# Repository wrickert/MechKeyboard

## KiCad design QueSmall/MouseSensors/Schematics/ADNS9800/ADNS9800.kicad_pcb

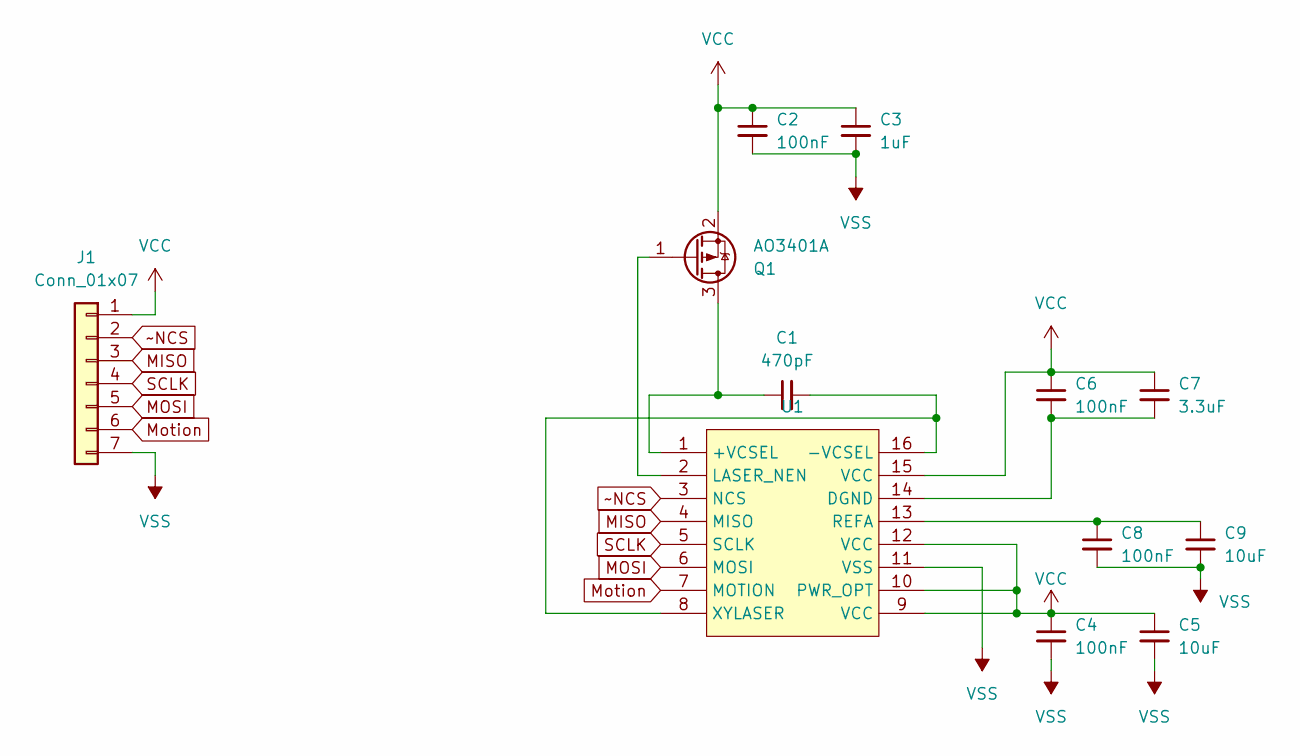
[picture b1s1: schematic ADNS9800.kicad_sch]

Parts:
C1: 470pF; C_0805_2012Metric
C2, C4, C6, C8: 100nF; C_0805_2012Metric
C3: 1uF; C_0805_2012Metric
C5, C9: 10uF; C_0805_2012Metric
C7: 3.3uF; C_0805_2012Metric
J1: Conn_01x07; PinHeader_1x07_P2.54mm_Vertical
Q1: AO3401A; SOT-23
U1: (no value)

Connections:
MISO: J1.3, U1.4 (MISO)
MOSI: J1.5, U1.6 (MOSI)
Motion: J1.6, U1.7 (MOTION)
unnamed: C1.1, Q1.3 (D), U1.1 (+VCSEL)
unnamed: Q1.1 (G), U1.2 (LASER_NEN)
unnamed: C1.2, U1.8 (XYLASER), U1.16 (-VCSEL)
unnamed: C6.2, C7.2, U1.14 (DGND)
unnamed: C8.1, C9.1, U1.13 (REFA)
SCLK: J1.4, U1.5 (SCLK)
VCC: C2.1, C3.1, C4.1, C5.1, C6.1, C7.1, J1.1, Q1.2 (S), U1.9 (VCC), U1.10 (PWR_OPT), U1.12 (VCC), U1.15 (VCC)
VSS: C2.2, C3.2, C4.2, C5.2, C8.2, C9.2, J1.7, U1.11 (VSS)
~NCS: J1.2, U1.3 (NCS)

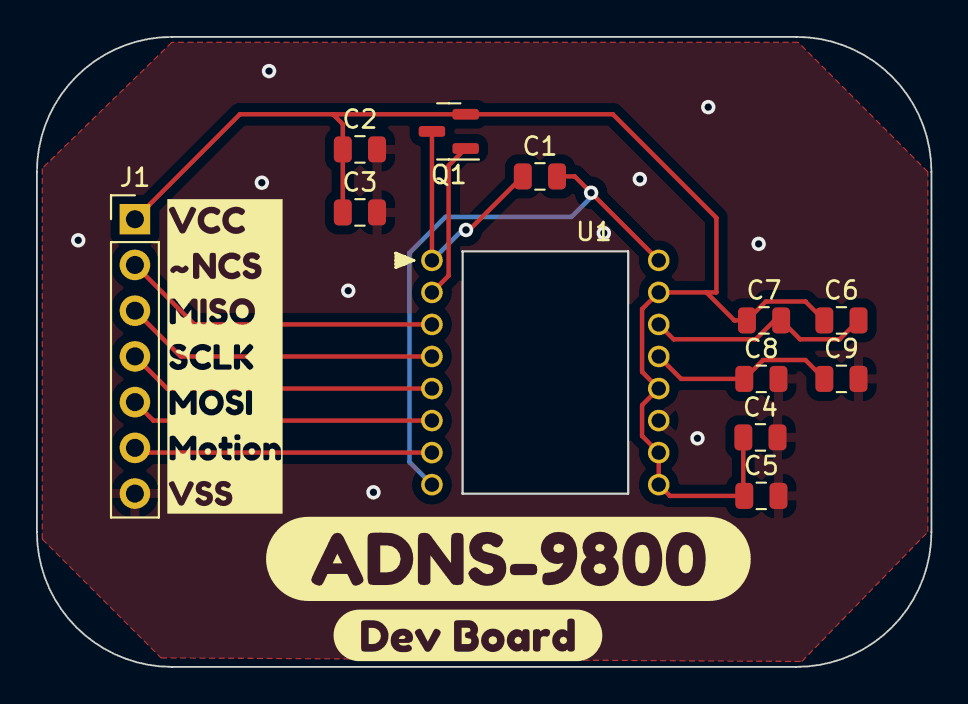
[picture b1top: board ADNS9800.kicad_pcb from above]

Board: 2 copper layers, 49.7 x 35.0 mm, 15 parts (0 on the bottom side), 12 nets.

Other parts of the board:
kibuzzard-65734003: G***; kibuzzard-65734003
kibuzzard-65734027: G***; kibuzzard-65734027
kibuzzard-65734037: G***; kibuzzard-65734037

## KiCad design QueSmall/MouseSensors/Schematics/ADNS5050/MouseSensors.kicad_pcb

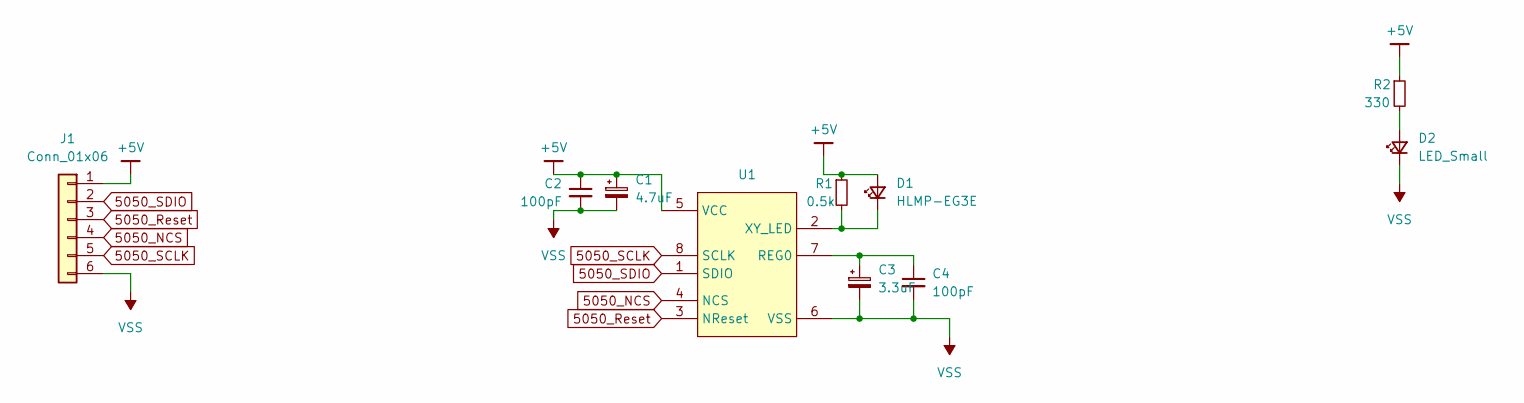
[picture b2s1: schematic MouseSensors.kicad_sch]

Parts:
C1: 4.7uF; C_0805_2012Metric
C2, C4: 100pF; C_0805_2012Metric
C3: 3.3uF; C_0805_2012Metric
D1: HLMP-EG3E; LED_D3.0mm
D2: LED_Small; LED_0805_2012Metric
J1: Conn_01x06; PinHeader_1x06_P2.54mm_Vertical
R1: 0.5k; R_0805_2012Metric
R2: 330; R_0805_2012Metric
U1: ADNS-5050

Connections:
5050_NCS: J1.4, U1.4 (NCS)
5050_Reset: J1.3, U1.3 (NReset)
5050_SCLK: J1.5, U1.8 (SCLK)
5050_SDIO: J1.2, U1.1 (SDIO)
+5V: C1.1, C2.1, D1.2 (A), J1.1, R1.1, R2.1, U1.5 (VCC)
unnamed: D1.1 (K), R1.2, U1.2 (XY_LED)
unnamed: D2.2 (A), R2.2
unnamed: C3.1, C4.1, U1.7 (REG0)
VSS: C1.2, C2.2, C3.2, C4.2, D2.1 (K), J1.6, U1.6 (VSS)

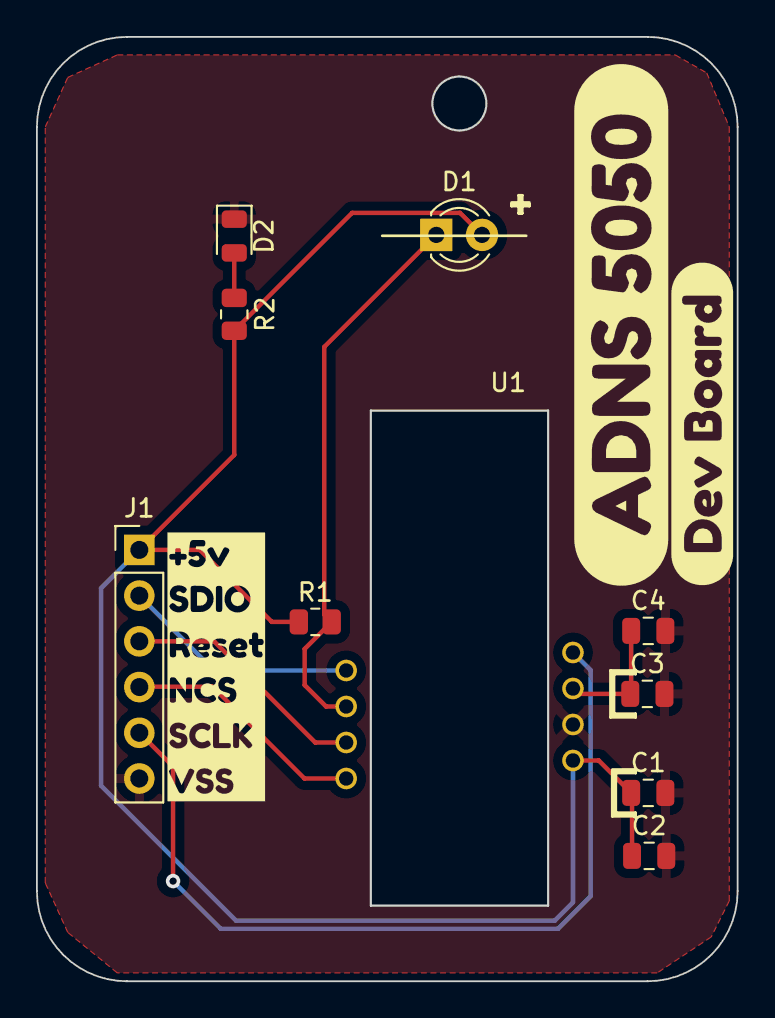
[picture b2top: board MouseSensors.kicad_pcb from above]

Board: 2 copper layers, 38.9 x 52.5 mm, 13 parts (0 on the bottom side), 9 nets.

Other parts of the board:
kibuzzard-65722F5A: G***; kibuzzard-65722F5A
kibuzzard-65722F43: G***; kibuzzard-65722F43
kibuzzard-65722FB8: G***; kibuzzard-65722FB8

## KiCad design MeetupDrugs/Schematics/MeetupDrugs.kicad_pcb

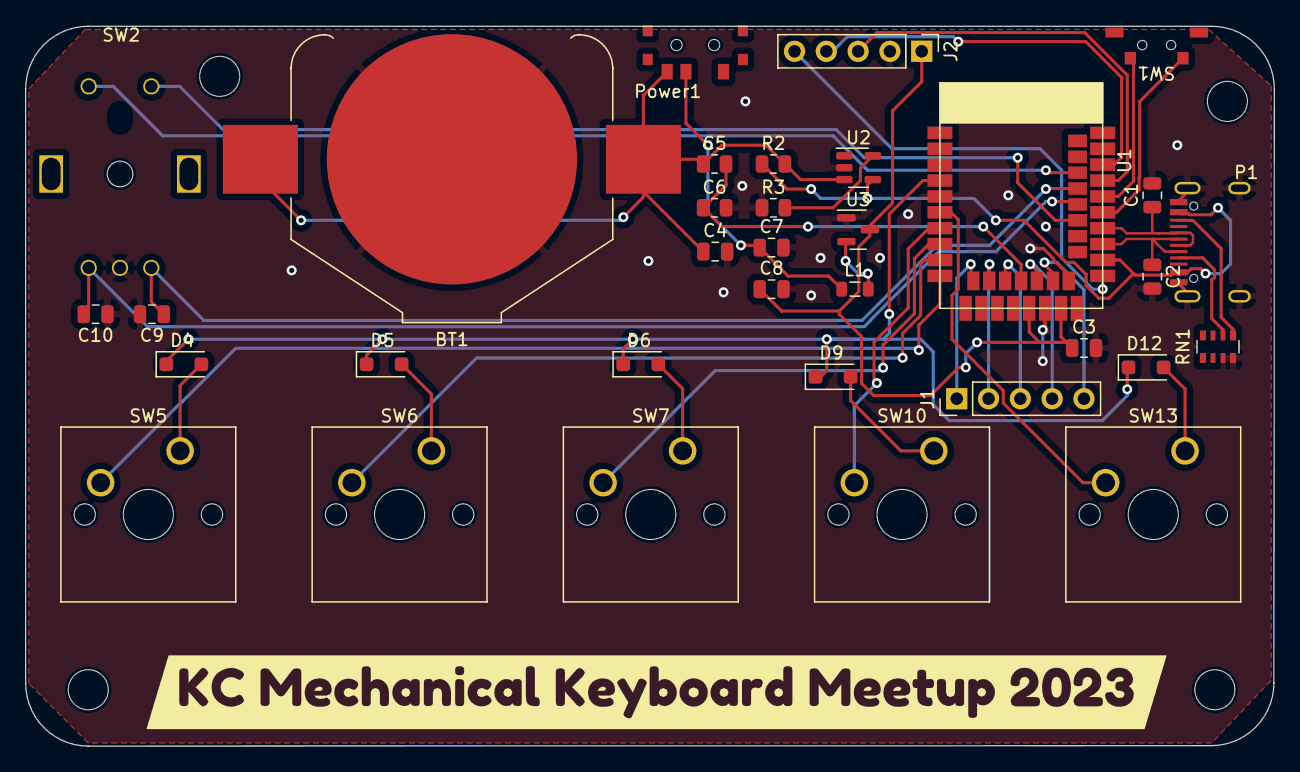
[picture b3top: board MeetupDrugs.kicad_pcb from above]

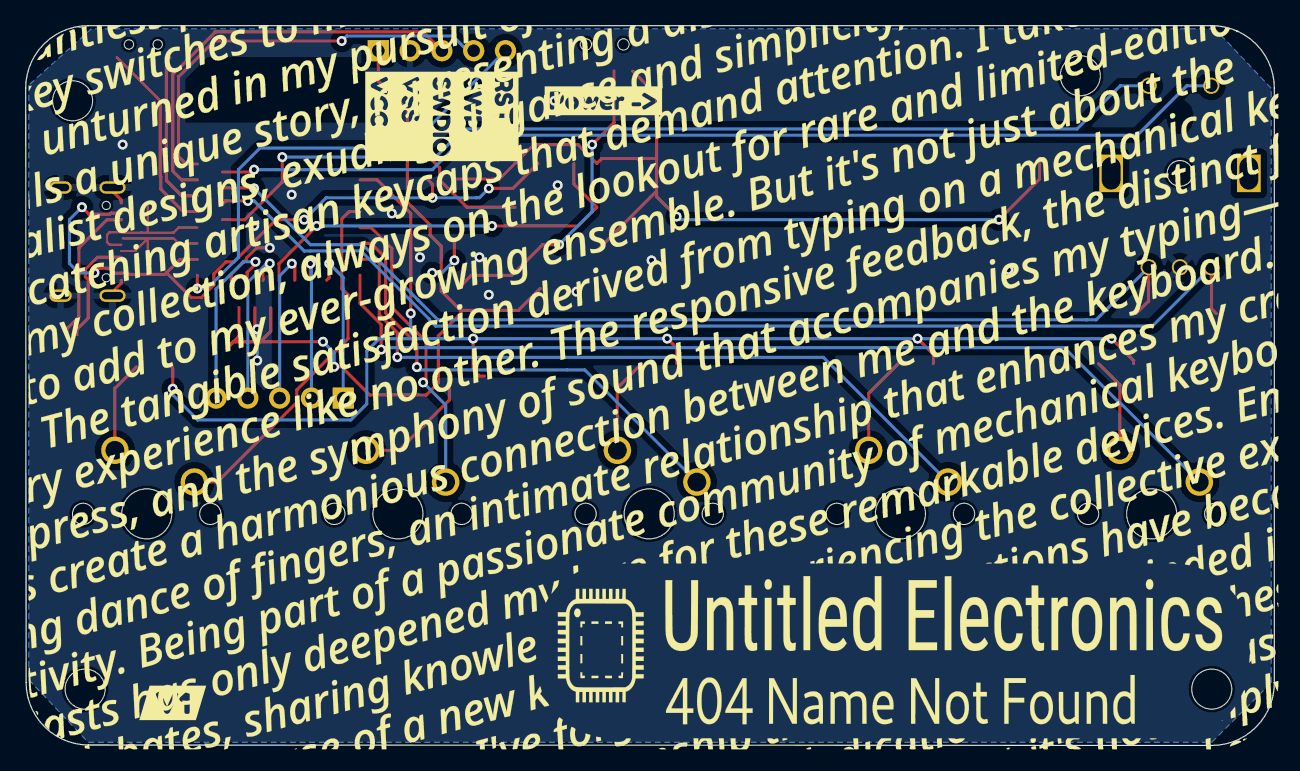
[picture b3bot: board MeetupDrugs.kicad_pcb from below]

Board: 2 copper layers, 99.8 x 57.5 mm, 39 parts (4 on the bottom side), 37 nets.

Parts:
BT1: Battery_Cell; BatteryHolder_Keystone_3008_1x2450
C1, C2: 20pF; C_0805_2012Metric
C3: 4.7uF; C_0805_2012Metric
C4, C7: 10uF; C_0805_2012Metric
C5: 800k; R_0805_2012Metric
C6: 2M; R_0805_2012Metric
C8: 22uF; C_0805_2012Metric
C9, C10: 100nF; C_0805_2012Metric
D4, D5, D6, D9, D12: D; D_SOD-123F
J1, J2: Conn_01x05; PinHeader_1x05_P2.54mm_Vertical
L1: 10uH; L_0805_2012Metric
P1: USB_C_Plug_corrected; USB_C_Receptical-Jing
Power1: SW3; SK-3296S_switch
R2: Charger Bypass; R_0805_2012Metric
R3: R_Small; R_0805_2012Metric
RN1: 5.1k; R_Array_Convex_4x0603
Ref**: Val**; MeetupBack
SW1: SW_SPST; TS36CA-0.7
SW2: Rotary_Encoder_Switch; EC11L1524E03_Rotary_Encoder
SW5, SW6, SW7, SW10, SW13: Switch; SW_Cherry_MX_1.00u_PCB
U1: E73-2G4M08S1C
U2: HX4055M; SOT-23-5
U3: SOT-23
kibuzzard-648A54B3: G***; kibuzzard-648A54B3
kibuzzard-648A54D0: G***; kibuzzard-648A54D0
kibuzzard-648A556D: G***; kibuzzard-648A556D
kibuzzard-648A5551: G***; kibuzzard-648A5551

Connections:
/C1: SW5.2, U1.10 (P0.30/A6)
/C2: SW6.2, U1.9 (P0.31/A7)
/C3: SW7.2, U1.8 (P0.29/A5)
/C4: SW10.2, U1.7 (P0.02/A0)
/C5: SW13.2, U1.6 (P1.13)
/R1: D4.1 (K), D5.1 (K), D6.1 (K), D9.1 (K), D12.1 (K), U1.4 (P0.28/A4)
/RotaryA: C9.1, SW2.B, U1.36 (P1.0)
/RotaryB: C10.2, SW2.A, U1.34 (P0.22)
/RotaryS1: SW2.S1, U1.38 (P1.02)
/RotaryS2: SW2.S2, U1.32 (P0.20)
D+: C1.1, P1.A6 (D+), P1.B6 (D+), U1.31 (D+)
D-: C2.1, P1.A7 (D-), P1.B7 (D-), U1.29 (D-)
unnamed: D4.2 (A), SW5.1
unnamed: D5.2 (A), SW6.1
unnamed: D6.2 (A), SW7.1
unnamed: D9.2 (A), SW10.1
unnamed: D12.2 (A), SW13.1
unnamed: J1.1, U1.12 (P0.26)
unnamed: J1.2, U1.14 (P0.06)
unnamed: J1.3, U1.16 (P0.08)
unnamed: J1.4, U1.20 (P0.12)
unnamed: J1.5, U1.22 (P0.07)
unnamed: P1.A5 (CC), RN1.6 (R3.2)
unnamed: P1.B5 (VCONN), RN1.5 (R4.2)
unnamed: C7.1, L1.1, Power1.2 (B)
unnamed: SW1.1 (A), U1.33 (P0.13)
unnamed: SW1.2 (B), U1.35 (P0.24)
unnamed: R3.2, U2.5 (PROG)
unnamed: L1.2, U3.2 (LX)
RST: J2.5, U1.26 (RST)
SWD: J2.4, U1.39 (SWD)
SWDIO: J2.3, U1.37 (SWDIO)
VBUS: P1.A4 (VBUS), P1.A9 (VBUS), P1.B4 (VBUS), P1.B9 (VBUS), R2.1, U1.27 (VBUS), U2.4 (VCC)
VBat: C5.2, C6.1, U1.18 (P0.04/A2)
VCC: C3.1, C8.1, J2.1, U1.19 (VDD), U1.23 (VDDH), U3.3 (VOUT)
VDDA: BT1.1 (+), C4.1, C5.1, Power1.1 (A), R2.2, U2.3 (Bat)
VSS: BT1.2 (-), C1.2, C2.2, C3.2, C4.2, C6.2, C7.2, C8.2, C9.2, C10.1, J2.2, P1.A1 (GND), P1.A12 (GND), P1.B1 (GND), P1.B12 (GND), P1.S1 (SHIELD), R3.1, RN1.3 (R3.1), RN1.4 (R4.1), SW2.C, U1.5 (GND), U1.21 (GND), U1.24 (GND), U2.2 (Gnd), U3.1 (VSS)

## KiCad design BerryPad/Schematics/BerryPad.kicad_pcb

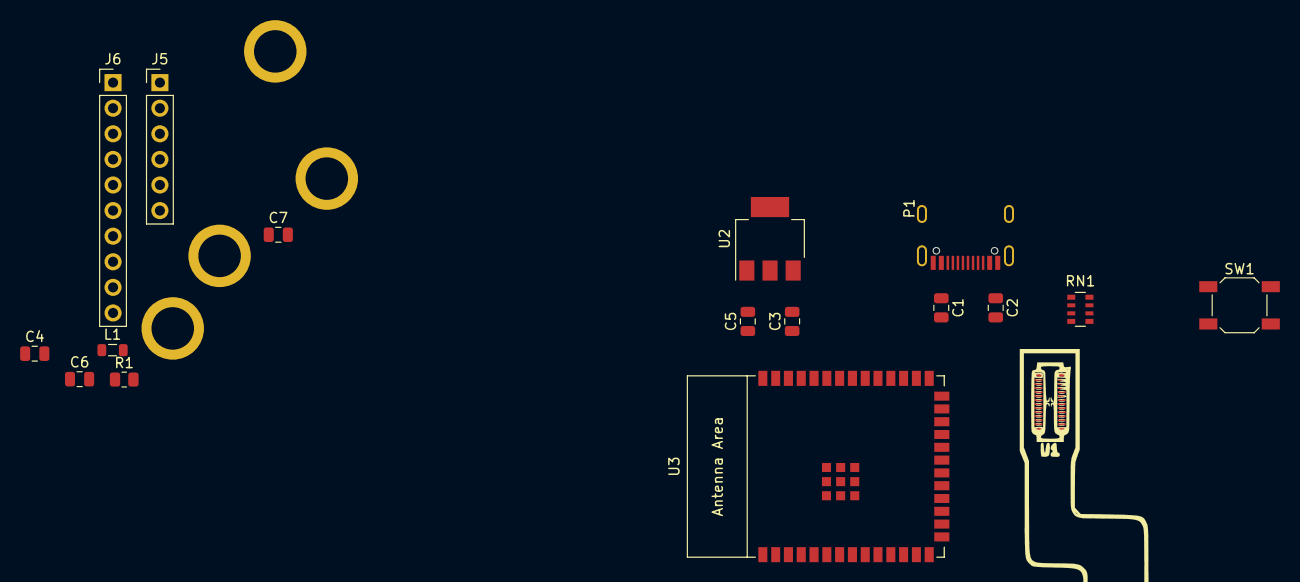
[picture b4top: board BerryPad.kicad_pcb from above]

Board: 2 copper layers, 22 parts (1 on the bottom side), 36 nets, no tracks yet.

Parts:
C1, C2: 20pF; C_0805_2012Metric
C3, C5: 1uF; C_0805_2012Metric
C4: 22uF; C_0805_2012Metric
C6, C7: 100nF; C_0805_2012Metric
J1, J2, J3, J4: Conn_01x01; SMD Spacer M2.5
J5: Program; PinHeader_1x06_P2.54mm_Vertical
J6: Conn_01x10; PinHeader_1x10_P2.54mm_Vertical
L1: L_Small; L_0805_2012Metric
P1: USB_C_Plug_corrected; USB_C_Receptical-Jing
R1: 1k; R_0805_2012Metric
RN1: 5.1k; R_Array_Convex_4x0603
Ref**: Val**; BerryPadKbd
SW1: Boot Mode; SW_SPST_SKQG_WithoutStem
U1: BBQ10KBD; BM14B(0.8)-24DS-0.4V(53)
U2: TLV1117-33; SOT-223-3_TabPin2
U3: ESP32-S2-SOLO

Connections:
1: J6.1, U3.39 (GPIO1/TOUCH1/ADC1_CH0)
2: J6.2, U3.38 (GPIO2/TOUCH2/ADC1_CH1)
3: J6.3, U3.15 (GPIO3/TOUCH3/ADC1_CH2)
4: J6.4, U3.35 (MTMS/GPIO42)
5: J6.5, U3.26 (GPIO45)
6: J6.6, U3.16 (GPIO46)
7: J6.7, U3.24 (SPIIO4/GPIO33/FSPIHD)
8: J6.8, U3.25 (SPIIO5/GPIO34/FSPICS0)
9: J6.9, U3.28 (SPIIO6/GPIO35/FSPID)
10: J6.10, U3.29 (SPIIO7/GPIO36/FSPICLK)
/D+: C1.1, P1.A6 (D+), P1.B6 (D+), U3.14 (GPIO20/U1CTS/ADC2_CH9/CLK_OUT1/USB_D+)
/D-: C2.1, P1.A7 (D-), P1.B7 (D-), U3.13 (GPIO19/U1RTS/ADC2_CH8/CLK_OUT2/USB_D-)
COL1: U1.7 (COL1), U3.4 (GPIO4/TOUCH4/ADC1_CH3)
COL2: U1.9 (COL2), U3.5 (GPIO5/TOUCH5/ADC1_CH4)
COL3: U1.10 (COL3), U3.6 (GPIO6/TOUCH6/ADC1_CH5)
COL4: U1.17 (COL4), U3.7 (GPIO7/TOUCH7/ADC1_CH6)
COL5: U1.19 (COL5), U3.12 (GPIO8/TOUCH8/ADC1_CH7)
LEDA1: U1.26 (LEDA_1_2), U3.9 (GPIO16/U0CTS/ADC2_CH5/XTAL_32K_N)
LEDA2: U1.24 (LEDA_3_4), U3.10 (GPIO17/U1TXD/ADC2_CH6/DAC_1)
unnamed: P1.A5 (CC), RN1.7 (R2.2)
unnamed: P1.B5 (VCONN), RN1.8 (R1.2)
unnamed: L1.1, U1.4 (AGND)
ROW1: U1.6 (ROW1), U3.17 (GPIO9/TOUCH9/ADC1_CH8/FSPIHD)
ROW2: U1.8 (ROW2), U3.18 (GPIO10/TOUCH10/ADC1_CH9/FSPICS0/FSPIIO4)
ROW3: U1.18 (ROW3), U3.19 (GPIO11/TOUCH11/ADC2_CH0/FSPID/FSPIIO5)
ROW4: U1.20 (ROW4), U3.20 (GPIO12/TOUCH12/ADC2_CH1/FSPICLK/FSPIIO6)
ROW5: U1.21 (ROW5), U3.21 (GPIO13/TOUCH13/ADC2_CH2/FSPIQ/FSPIIO7)
ROW6: U1.22 (ROW6), U3.22 (GPIO14/TOUCH14/ADC2_CH3/FSPIWP/FSPIDQS)
ROW7: U1.27 (ROW7), U3.8 (GPIO15/U0RTS/ADC2_CH4/XTAL_32K_P)
RX: J5.5, U3.36 (U0RXD/GPIO44/CLK_OUT2)
Reset: C7.1, J5.6, R1.1, U3.3 (EN)
TX: J5.4, U3.37 (U0TXD/GPIO43/CLK_OUT1)
TopLeft: J5.3, SW1.2, U3.27 (GPIO0)
VBUS: C3.2, P1.A4 (VBUS), P1.A9 (VBUS), P1.B4 (VBUS), P1.B9 (VBUS), U2.3 (VI)
VCC: C4.1, C5.2, C6.1, J5.1, R1.2, U1.2 (MIC_VDD), U2.2 (VO), U3.2 (3V3)
VSS: C1.2, C2.2, C3.1, C4.2, C5.1, C6.2, C7.2, J5.2, L1.2, P1.A1 (GND), P1.A12 (GND), P1.B1 (GND), P1.B12 (GND), P1.S1 (SHIELD), RN1.1 (R1.1), RN1.2 (R2.1), SW1.1, U1.1 (GND), U1.5 (GND), U1.11 (GND), U1.12 (GND), U1.13 (GND), U1.14 (GND), U1.15 (GND), U1.16 (GND), U1.23 (LEDK_2_3), U1.25 (LEDK_1_4), U1.28 (GND), U2.1 (GND), U3.1 (GND), U3.40 (GND), U3.41 (GND)

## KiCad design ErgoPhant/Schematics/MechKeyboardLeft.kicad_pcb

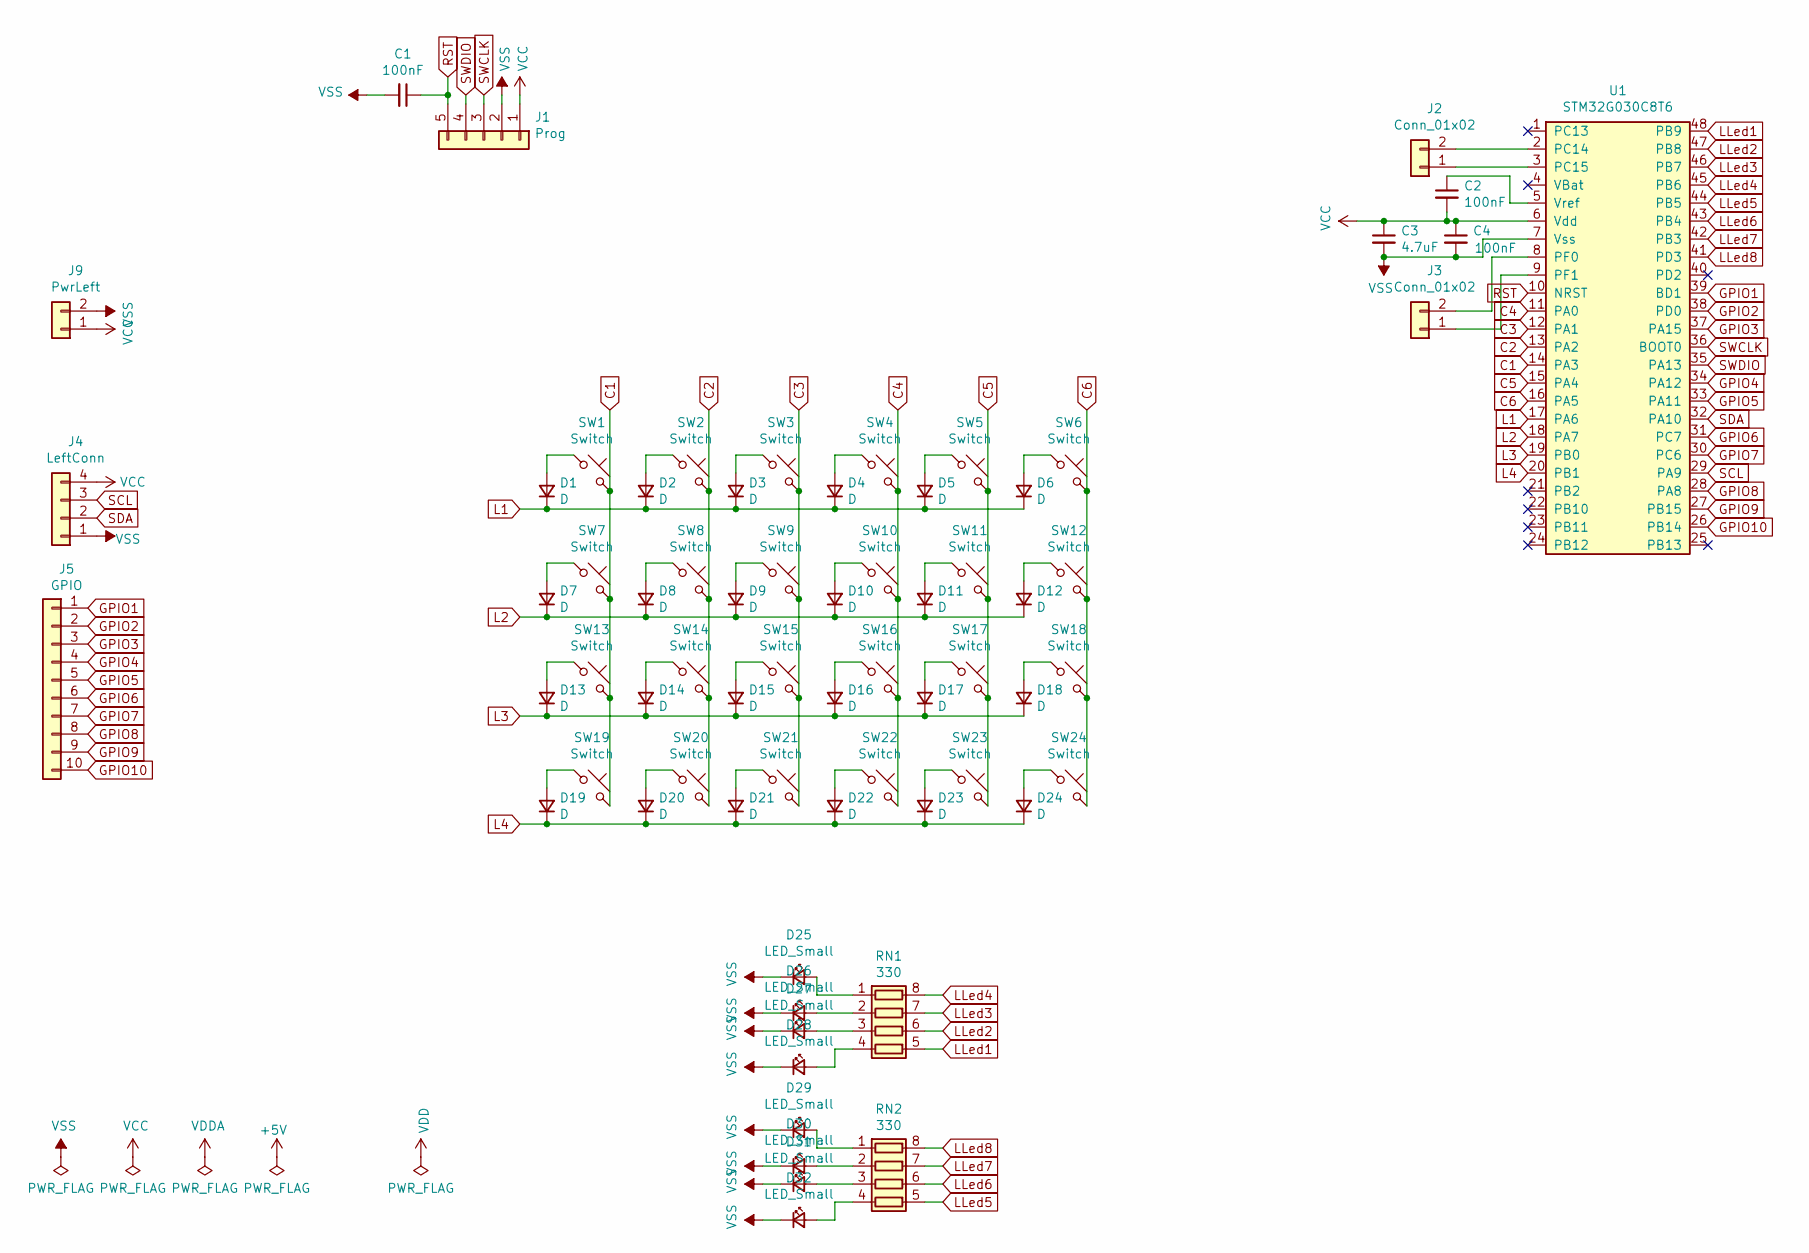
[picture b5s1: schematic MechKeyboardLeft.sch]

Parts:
C1, C2, C4: 100nF; C_0805_2012Metric
C3: 4.7uF; C_0805_2012Metric
D1, D2, D3, D4, D5, D6, D7, D8, D9, D10, D11, D12, D13, D14, D15, D16, D17, D18, D19, D20, D21, D22, D23, D24: D; D_0805_2012Metric
D25, D26, D27, D28, D29, D30, D31, D32: LED_Small; LED_0805_2012Metric
J1: Prog; PinHeader_1x05_P2.54mm_Vertical
J2: Conn_01x02; PinHeader_1x02_P2.54mm_Vertical
J3: Conn_01x02; PinHeader_1x02_P1.00mm_Vertical
J4: LeftConn; PJ-320D-4A_TRRS3.5
J5: GPIO; PinHeader_1x10_P1.00mm_Vertical
J9: PwrLeft; PinHeader_1x02_P2.54mm_Vertical
RN1, RN2: 330; R_Array_Concave_4x0603
SW1, SW2, SW3, SW4, SW5, SW6, SW7, SW8, SW9, SW10, SW11, SW12, SW13, SW14, SW15, SW16, SW17, SW18, SW19, SW20, SW21, SW22, SW23, SW24: Switch; KailhChocolateV2
U1: STM32G030C8T6; LQFP-48_7x7mm_P0.5mm

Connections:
C1: SW1.2, SW7.2, SW13.2, SW19.2, U1.14 (PA3)
C2: SW2.2, SW8.2, SW14.2, SW20.2, U1.13 (PA2)
C3: SW3.2, SW9.2, SW15.2, SW21.2, U1.12 (PA1)
C4: SW4.2, SW10.2, SW16.2, SW22.2, U1.11 (PA0)
C5: SW5.2, SW11.2, SW17.2, SW23.2, U1.15 (PA4)
C6: SW6.2, SW12.2, SW18.2, SW24.2, U1.16 (PA5)
GPIO1: J5.1, U1.39 (BD1)
GPIO2: J5.2, U1.38 (PD0)
GPIO3: J5.3, U1.37 (PA15)
GPIO4: J5.4, U1.34 (PA12)
GPIO5: J5.5, U1.33 (PA11)
GPIO6: J5.6, U1.31 (PC7)
GPIO7: J5.7, U1.30 (PC6)
GPIO8: J5.8, U1.28 (PA8)
GPIO9: J5.9, U1.27 (PB15)
GPIO10: J5.10, U1.26 (PB14)
L1: D1.1 (K), D2.1 (K), D3.1 (K), D4.1 (K), D5.1 (K), D6.1 (K), U1.17 (PA6)
L2: D7.1 (K), D8.1 (K), D9.1 (K), D10.1 (K), D11.1 (K), D12.1 (K), U1.18 (PA7)
L3: D13.1 (K), D14.1 (K), D15.1 (K), D16.1 (K), D17.1 (K), D18.1 (K), U1.19 (PB0)
L4: D19.1 (K), D20.1 (K), D21.1 (K), D22.1 (K), D23.1 (K), D24.1 (K), U1.20 (PB1)
LLed1: RN1.5 (R4.2), U1.48 (PB9)
LLed2: RN1.6 (R3.2), U1.47 (PB8)
LLed3: RN1.7 (R2.2), U1.46 (PB7)
LLed4: RN1.8 (R1.2), U1.45 (PB6)
LLed5: RN2.5 (R4.2), U1.44 (PB5)
LLed6: RN2.6 (R3.2), U1.43 (PB4)
LLed7: RN2.7 (R2.2), U1.42 (PB3)
LLed8: RN2.8 (R1.2), U1.41 (PD3)
unnamed: C2.1, U1.5 (Vref)
unnamed: D1.2 (A), SW1.1
unnamed: D2.2 (A), SW2.1
unnamed: D3.2 (A), SW3.1
unnamed: D4.2 (A), SW4.1
unnamed: D5.2 (A), SW5.1
unnamed: D6.2 (A), SW6.1
unnamed: D7.2 (A), SW7.1
unnamed: D8.2 (A), SW8.1
unnamed: D9.2 (A), SW9.1
unnamed: D10.2 (A), SW10.1
unnamed: D11.2 (A), SW11.1
unnamed: D12.2 (A), SW12.1
unnamed: D13.2 (A), SW13.1
unnamed: D14.2 (A), SW14.1
unnamed: D15.2 (A), SW15.1
unnamed: D16.2 (A), SW16.1
unnamed: D17.2 (A), SW17.1
unnamed: D18.2 (A), SW18.1
unnamed: D19.2 (A), SW19.1
unnamed: D20.2 (A), SW20.1
unnamed: D21.2 (A), SW21.1
unnamed: D22.2 (A), SW22.1
unnamed: D23.2 (A), SW23.1
unnamed: D24.2 (A), SW24.1
unnamed: D25.2 (A), RN1.1 (R1.1)
unnamed: D26.2 (A), RN1.2 (R2.1)
unnamed: D27.2 (A), RN1.3 (R3.1)
unnamed: D28.2 (A), RN1.4 (R4.1)
unnamed: D29.2 (A), RN2.1 (R1.1)
unnamed: D30.2 (A), RN2.2 (R2.1)
unnamed: D31.2 (A), RN2.3 (R3.1)
unnamed: D32.2 (A), RN2.4 (R4.1)
unnamed: J2.1, U1.3 (PC15)
unnamed: J2.2, U1.2 (PC14)
unnamed: J3.1, U1.9 (PF1)
unnamed: J3.2, U1.8 (PF0)
RST: C1.1, J1.5, U1.10 (NRST)
SCL: J4.3, U1.29 (PA9)
SDA: J4.2, U1.32 (PA10)
SWCLK: J1.3, U1.36 (BOOT0)
SWDIO: J1.4, U1.35 (PA13)
VCC: C2.2, C3.1, C4.1, J1.1, J4.4, J9.1, U1.6 (Vdd)
VSS: C1.2, C3.2, C4.2, D25.1 (K), D26.1 (K), D27.1 (K), D28.1 (K), D29.1 (K), D30.1 (K), D31.1 (K), D32.1 (K), J1.2, J4.1, J9.2, U1.7 (Vss)

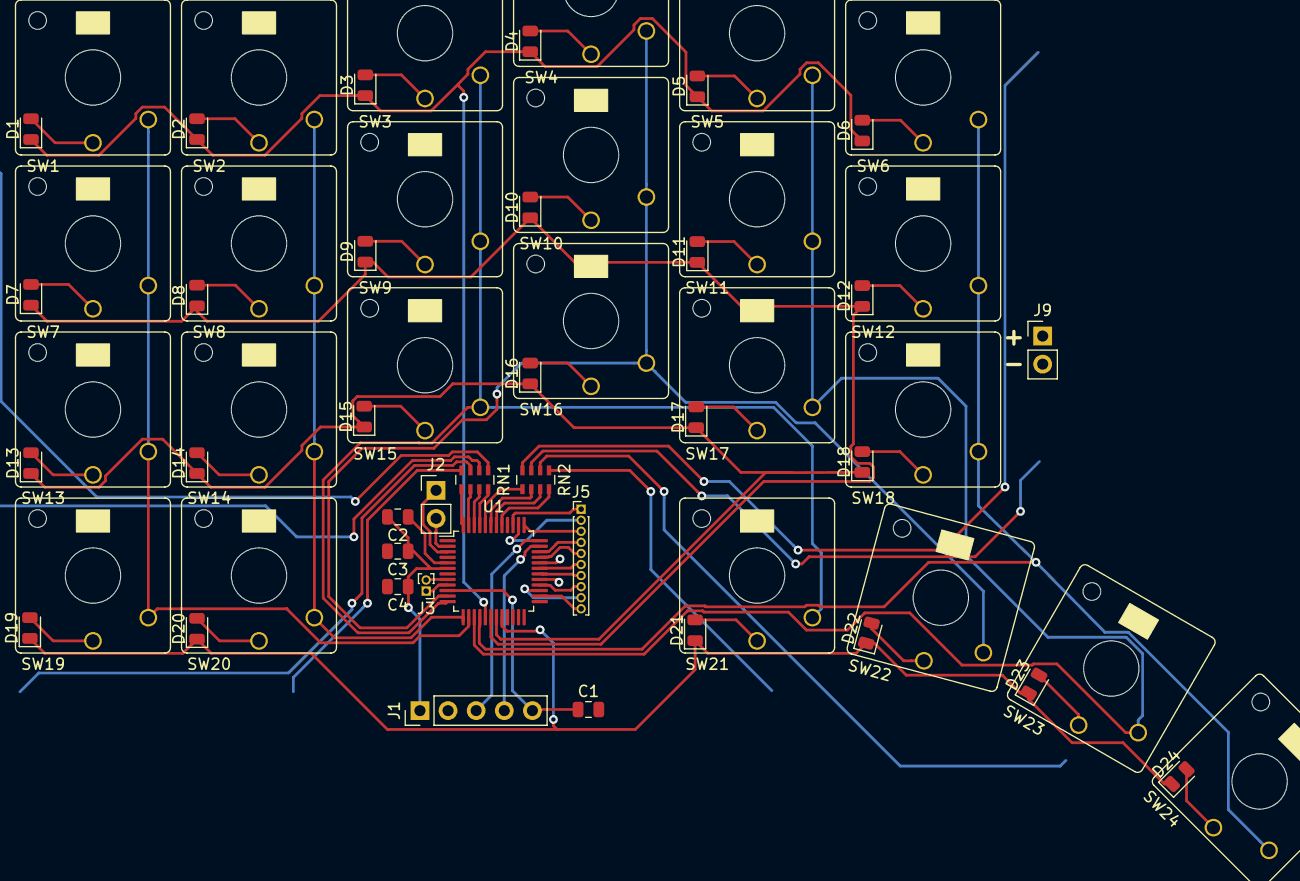
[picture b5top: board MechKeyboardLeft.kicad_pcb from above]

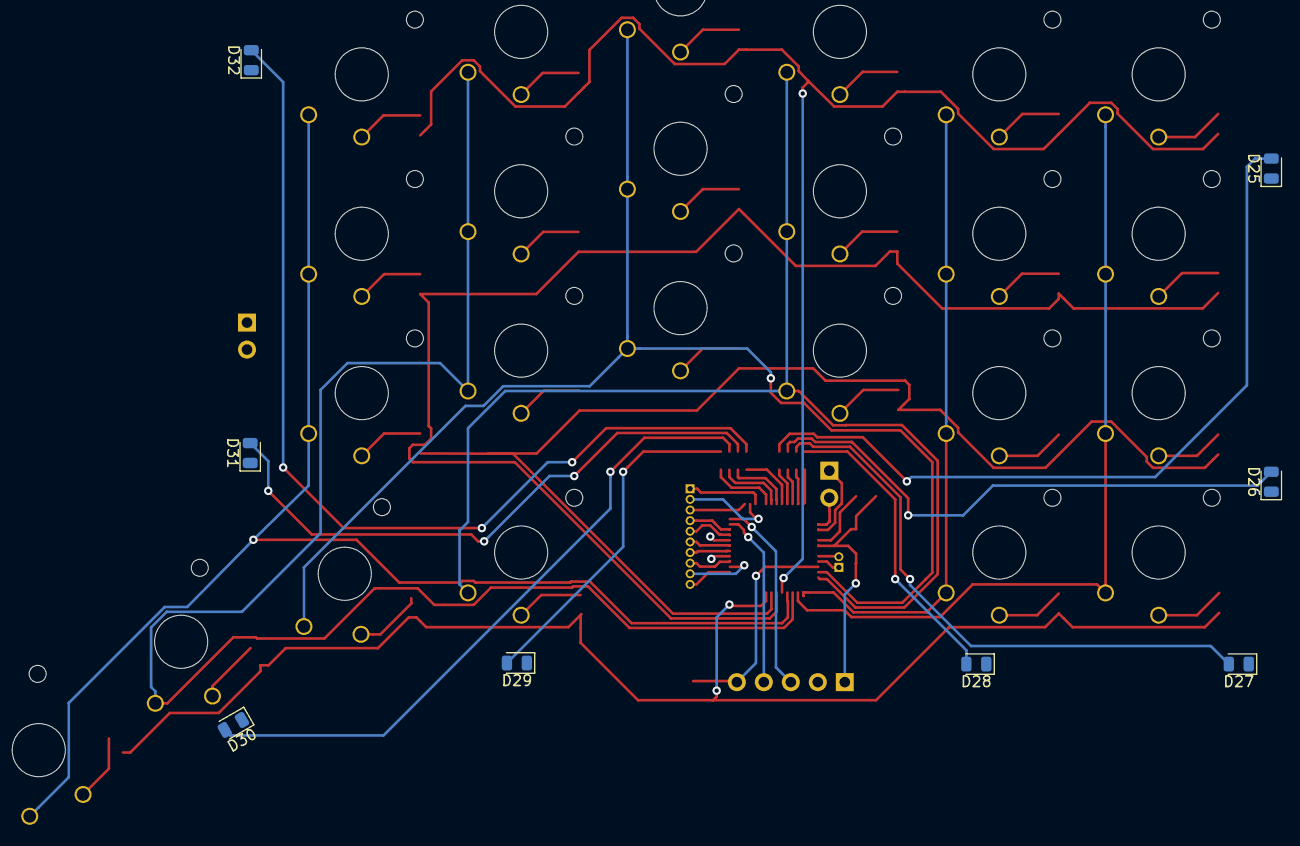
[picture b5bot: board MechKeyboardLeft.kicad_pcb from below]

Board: 2 copper layers, 68 parts (8 on the bottom side), 70 nets.

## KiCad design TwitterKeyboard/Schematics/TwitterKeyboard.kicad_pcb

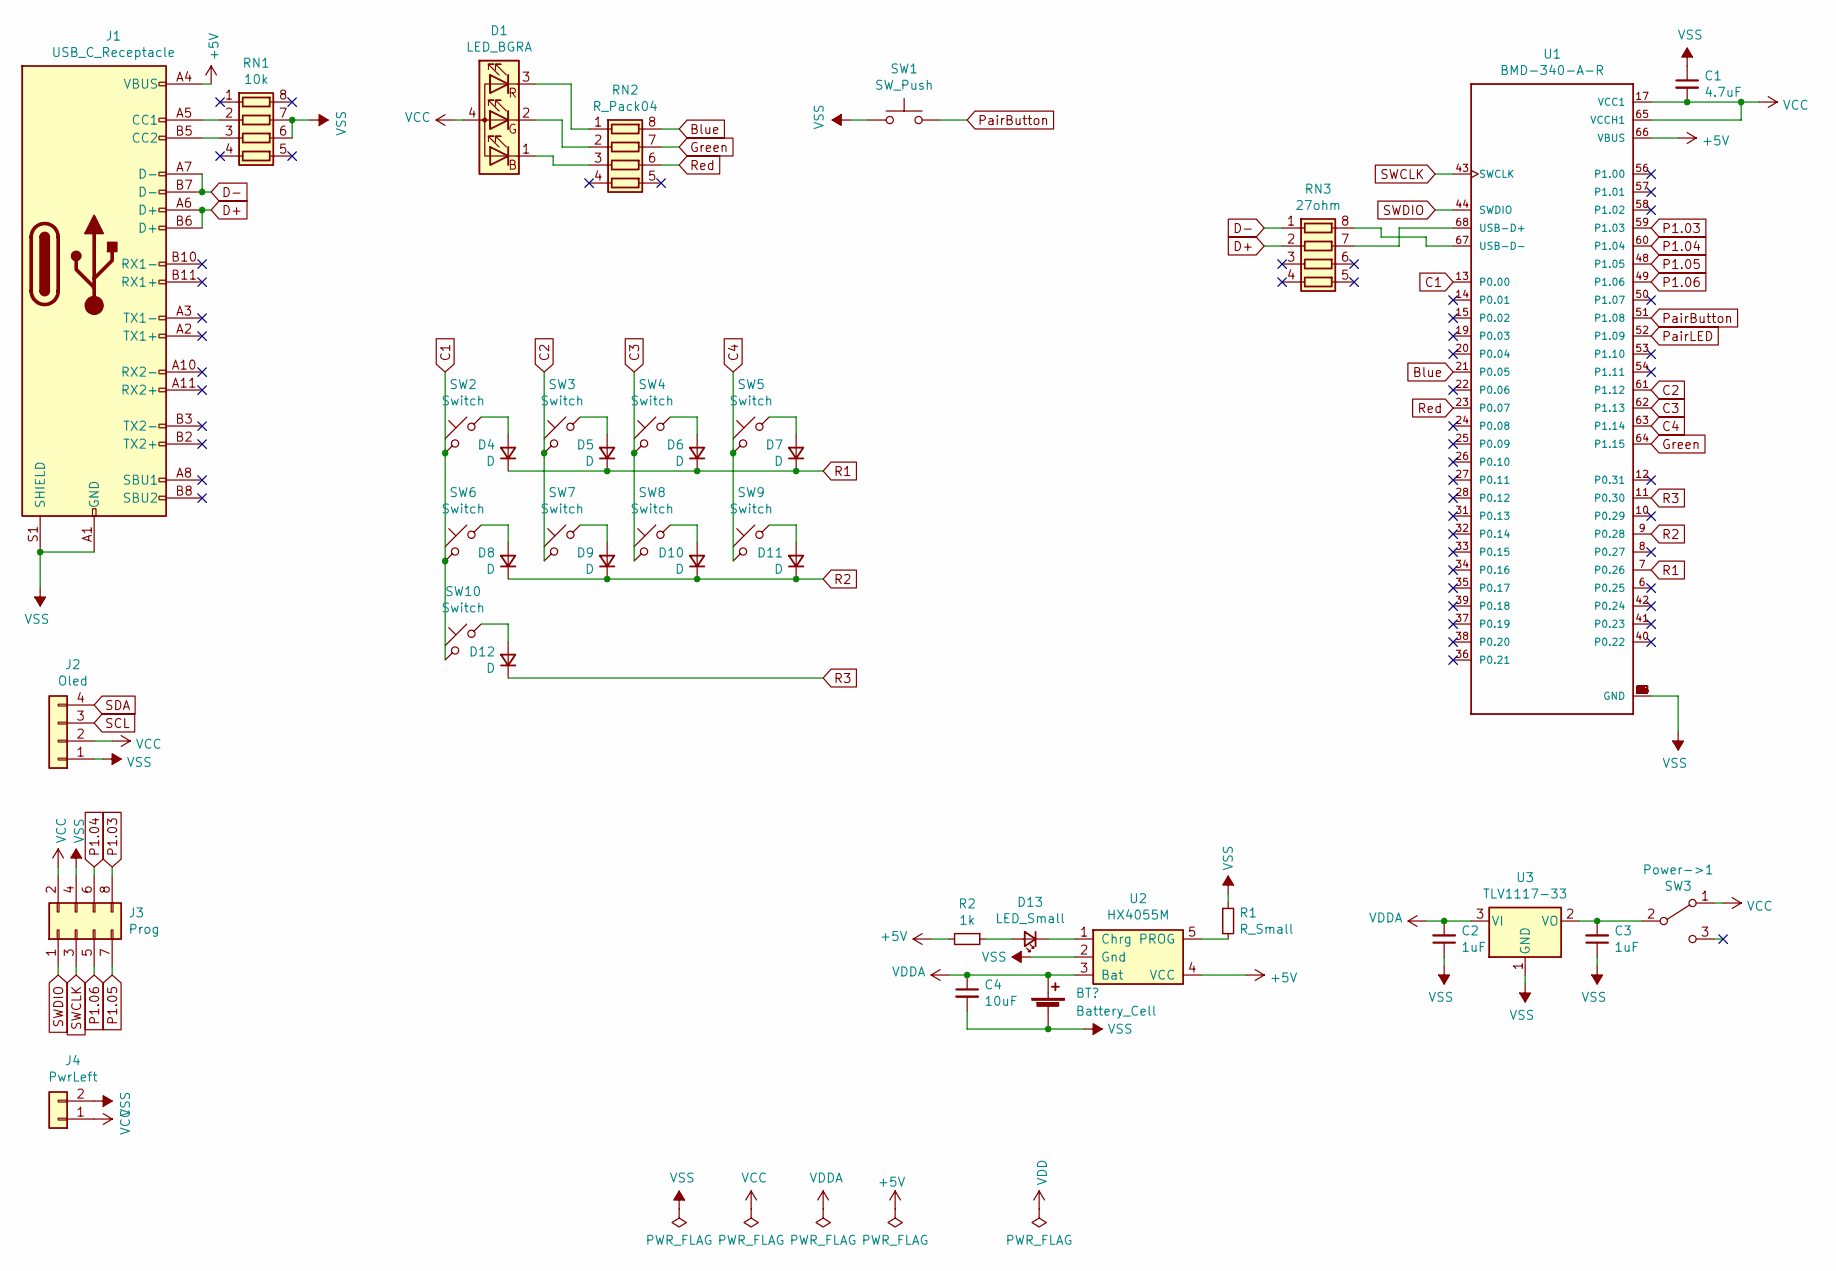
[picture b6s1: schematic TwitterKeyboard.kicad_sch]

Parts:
C1: 4.7uF; C_0805_2012Metric
C2, C3: 1uF; C_0805_2012Metric
C4: 10uF; C_0805_2012Metric
D1: LED_BGRA; EKINGLUX-E6
D4, D5, D6, D7, D8, D9, D10, D11, D12: D; D_0805_2012Metric
D13: LED_Small; LED_0805_2012Metric
J1: USB_C_Receptacle; USB_C_Receptical-Jing
J2: Oled
J3: Prog; SOIC_clipProgSmall
J4: PwrLeft; PinHeader_1x02_P2.54mm_Vertical
Power->1: SW3; SK-3296S_switch
R1: R_Small; R_0805_2012Metric
R2: 1k; R_0805_2012Metric
RN1: 10k; R_Array_Concave_4x0603
RN2: R_Pack04; R_Array_Concave_4x0603
RN3: 27ohm; R_Array_Convex_4x0603
SW1: SW_Push; 1TS002E-2500-2500-CT-HYP-Button
SW2, SW3, SW4, SW5, SW6, SW7, SW8, SW9, SW10: Switch; KailhChocolateV2
U1: BMD-340-A-R; RIGADO_BMD-340-A-R
U2: HX4055M; SOT-23-5
U3: TLV1117-33; SOT-223-3_TabPin2

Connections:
+5V: J1.A4 (VBUS), J1.A9 (VBUS), J1.B4 (VBUS), J1.B9 (VBUS), R2.2, U1.66 (VBUS), U2.4 (VCC)
Blue: RN2.8 (R1.2), U1.21 (P0.05)
C1: SW2.2, SW6.2, SW10.2, U1.13 (P0.00)
C2: SW3.2, SW7.2, U1.61 (P1.12)
C3: SW4.2, SW8.2, U1.62 (P1.13)
C4: SW5.2, SW9.2, U1.63 (P1.14)
D+: J1.A6 (D+), J1.B6 (D+), RN3.2 (R2.1)
D-: J1.A7 (D-), J1.B7 (D-), RN3.1 (R1.1)
Green: RN2.7 (R2.2), U1.64 (P1.15)
unnamed 9: C3.2, Power->1.2 (B), U3.2 (VO); also elsewhere on the board
unnamed: D1.1 (BK), RN2.3 (R3.1)
unnamed: D1.2 (GK), RN2.2 (R2.1)
unnamed: D1.3 (RK), RN2.1 (R1.1)
unnamed: D4.2 (A), SW2.1
unnamed: D5.2 (A), SW3.1
unnamed: D6.2 (A), SW4.1
unnamed: D7.2 (A), SW5.1
unnamed: D8.2 (A), SW6.1
unnamed: D9.2 (A), SW7.1
unnamed: D10.2 (A), SW8.1
unnamed: D11.2 (A), SW9.1
unnamed: D12.2 (A), SW10.1
unnamed: D13.1 (K), U2.1 (Chrg)
unnamed: D13.2 (A), R2.1
unnamed: J1.A5 (CC1), RN1.2 (R2.1)
unnamed: J1.B5 (CC2), RN1.3 (R3.1)
unnamed: R1.2, U2.5 (PROG)
unnamed: RN3.7 (R2.2), U1.68 (USB-D+)
unnamed: RN3.8 (R1.2), U1.67 (USB-D-)
P1.03: J3.8, U1.59 (P1.03)
P1.04: J3.6, U1.60 (P1.04)
P1.05: J3.7, U1.48 (P1.05)
P1.06: J3.5, U1.49 (P1.06)
PairButton: SW1.2, U1.51 (P1.08); also elsewhere on the board
PairLED: U1.52 (P1.09)
R1: D4.1 (K), D5.1 (K), D6.1 (K), D7.1 (K), U1.7 (P0.26)
R2: D8.1 (K), D9.1 (K), D10.1 (K), D11.1 (K), U1.9 (P0.28)
R3: D12.1 (K), U1.11 (P0.30)
Red: RN2.6 (R3.2), U1.23 (P0.07)
SCL: J2.3
SDA: J2.4
SWCLK: J3.3, U1.43 (SWCLK)
SWDIO: J3.1, U1.44 (SWDIO)
VCC: C1.2, D1.4 (A), J2.2, J3.2, J4.1, Power->1.1 (A), U1.17 (VCC1), U1.65 (VCCH1); also elsewhere on the board
VDDA: C2.2, C4.1, U2.3 (Bat), U3.3 (VI); also elsewhere on the board
VSS: C1.1, C2.1, C3.1, C4.2, J1.A1 (GND), J1.A12 (GND), J1.B1 (GND), J1.B12 (GND), J1.S1 (SHIELD), J2.1, J3.4, J4.2, R1.1, RN1.6 (R3.2), RN1.7 (R2.2), SW1.1, U1.1 (GND), U1.2 (GND), U1.3 (GND), U1.4 (GND), U1.5 (GND), U1.16 (GND), U1.18 (GND), U1.29 (GND), U1.30 (GND), U1.45 (GND), U1.46 (GND), U1.47 (GND), U1.55 (GND), U2.2 (Gnd), U3.1 (GND); also elsewhere on the board

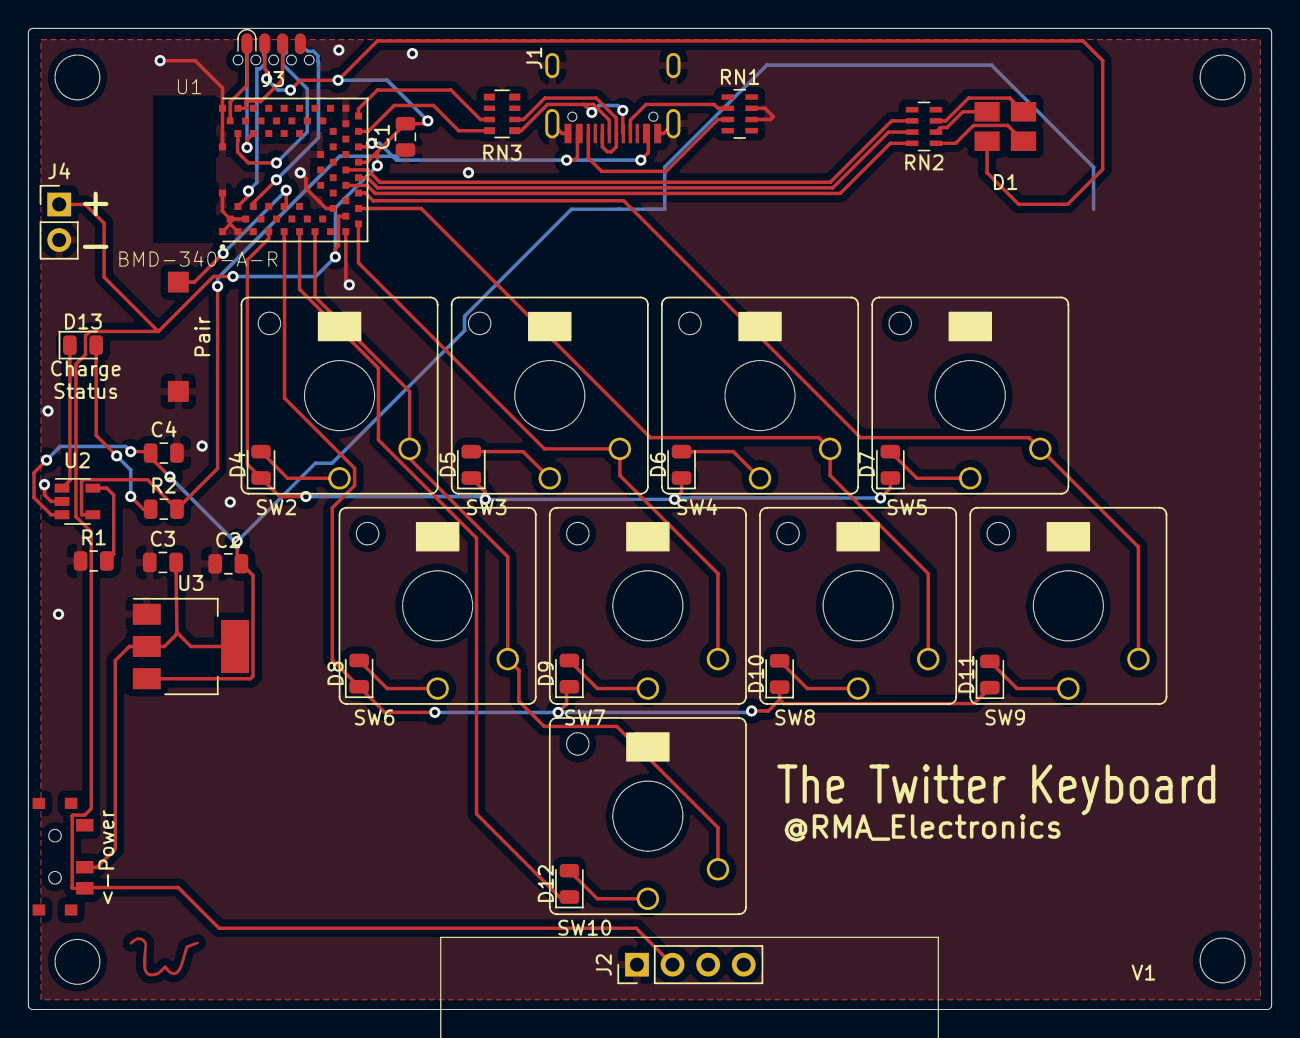
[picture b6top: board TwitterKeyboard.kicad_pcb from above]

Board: 2 copper layers, 88.7 x 70.0 mm, 40 parts (1 on the bottom side), 43 nets.

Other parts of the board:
<-Power: SW3; SK-3296S_switch
BT1: LIR2450; BatteryHolder_Keystone_3008_1x2450
Pair: SW_Push; 1TS002E-2500-2500-CT-HYP-Button
Ref**: Val**; W

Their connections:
unnamed 9: <-Power.2; also elsewhere on the board
PairButton: Pair.2; also elsewhere on the board
VCC: <-Power.1; also elsewhere on the board
VDDA: BT1.1; also elsewhere on the board
VSS: BT1.2, Pair.1; also elsewhere on the board
